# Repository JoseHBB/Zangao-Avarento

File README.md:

# Zangão Avarento

Wiki pública do projeto de TCC de automação industrial focado no desenvolvimento de um drone de baixo custo controlado por smartphone.

## Sobre

O Zangão Avarento nasceu como um projeto de TCC com o objetivo de demonstrar que era possível montar uma plataforma de voo com controle por celular utilizando componentes acessíveis, fabricação própria da placa e desenvolvimento do firmware e do aplicativo.

Este repositório funciona como a documentação pública do projeto. Aqui estão reunidos o histórico de desenvolvimento, os arquivos de eletrônica e PCB, os códigos do Arduino, os arquivos do aplicativo, imagens do processo e o relatório final.

## Navegação da wiki

- [Visão geral do projeto](Projeto.md)
- [Construção mecânica e estrutura](Construcao_Mecanica.md)
- [Firmware e lógica de controle no Arduino](Arduino_Reference.md)
- [Esquema elétrico e PCB no KiCad](KicadSchemePCB_Reference.md)
- [Aplicativo Android](App_Reference.md)
- [Galeria de imagens](Galeria.md)
- [Arquivos e recursos do repositório](Arquivos_e_Recursos.md)

## Estrutura resumida

- `Arduino/`: códigos e rascunhos do firmware.
- `App/`: arquivo-fonte do app no MIT App Inventor e APK gerado.
- `Kicad Scheme-PCB/`: projeto eletrônico e layout da placa.
- `Images/`: imagens de protótipos, placa, estrutura e esquemas.
- `Videos/`: vídeos de testes das funções e demonstração de voo.
- `Apresentação TCC Drone.pptx`: apresentação final do TCC.
- `Relatório.pdf`: versão do relatório final do trabalho.

## Criadores do projeto

- Guilherme Faria da Silva
- João Vinícius da Silva
- José Henrique Batista Borges

## Contato

Qualquer dúvida sobre o projeto:

- [José Henrique](https://github.com/JoseHBB)
- `josehenribb@gmail.com`

## Licença

Este repositório utiliza a licença MIT para fins de estudo, pesquisa, uso pessoal e uso comercial conforme os termos do arquivo [LICENSE](LICENSE).

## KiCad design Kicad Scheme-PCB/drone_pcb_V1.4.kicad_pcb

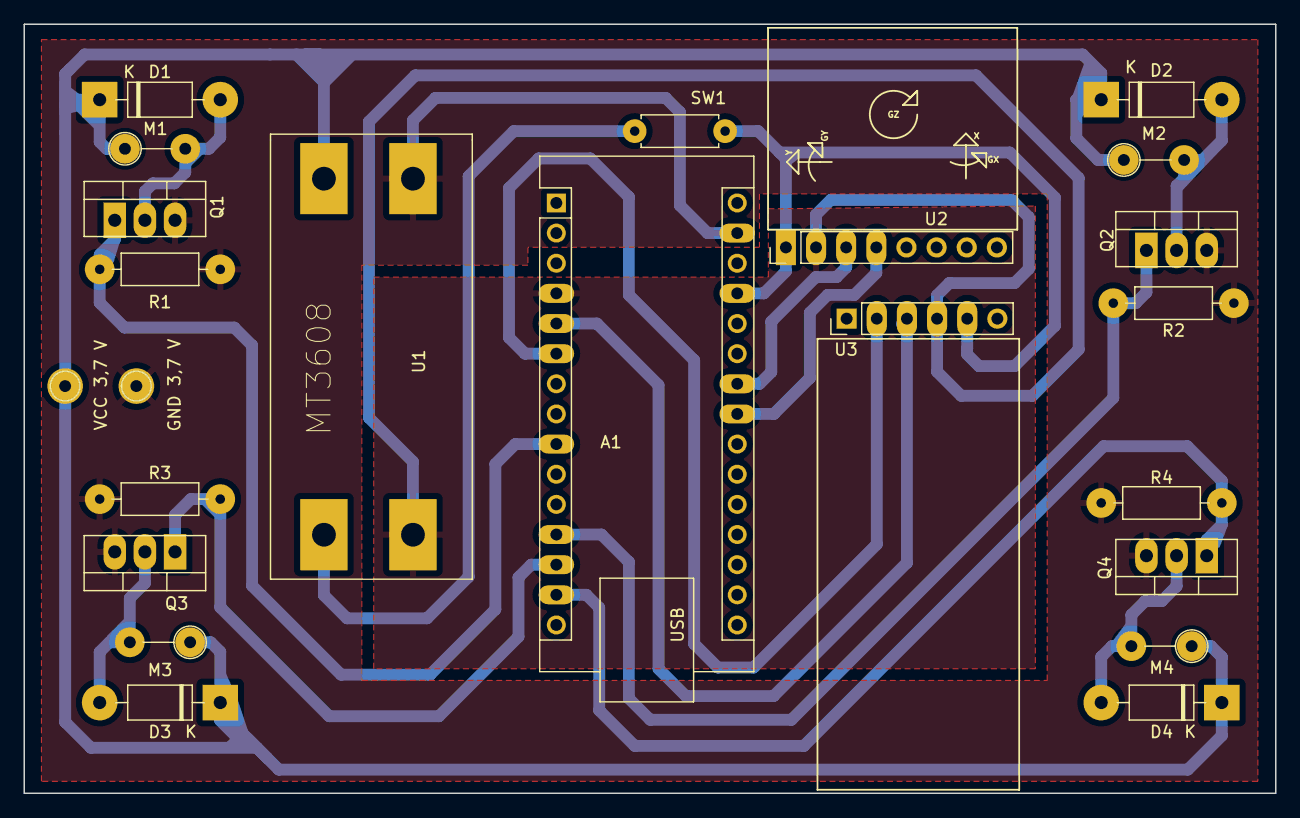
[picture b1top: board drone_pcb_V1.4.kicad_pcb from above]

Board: 2 copper layers, 105.4 x 64.8 mm, 23 parts (0 on the bottom side), 17 nets.

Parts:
A1: Arduino Nano; Arduino_Nano
D1, D2, D3, D4: 1N4007; D_DO-41_SOD81_P10.16mm_Horizontal
GND 3,7 V: Pin_D1.0mm_L10.0mm
M1, M2, M3, M4: Motor; R_Axial_DIN0207_L6.3mm_D2.5mm_P5.08mm_Vertical
Q1, Q2, Q3, Q4: IRF640; TO-220-3_Vertical
R1, R2, R3, R4: 1KΩ; R_Axial_DIN0207_L6.3mm_D2.5mm_P10.16mm_Horizontal
SW1: Switch; R_Axial_DIN0207_L6.3mm_D2.5mm_P7.62mm_Horizontal
U1: Step Up; MT3608
U2: Gyroscope; PinHeader_1x08_P2.54mm_Vertical
U3: HC-06; PinHeader_1x06_P2.54mm_Vertical
VCC 3,7 V: Pin_D1.0mm_L10.0mm

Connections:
GND: A1.29 (GND), GND 3,7 V.1, Q1.3 (S), Q2.3 (S), Q3.3 (S), Q4.3 (S), R1.2, R2.2, R3.2, R4.2, U1.2 (V_in-)
GND_5V: A1.4 (GND), U1.4 (V_out-), U2.2 (GND), U3.4 (GND)
M1-: D1.2 (A), M1.2 (-), Q1.2 (D)
M2-: D2.2 (A), M2.2 (-), Q2.2 (D)
M3-: D3.2 (A), M3.2 (-), Q3.2 (D)
M4-: D4.2 (A), M4.2 (-), Q4.2 (D)
PWM_D6: A1.9 (D6), Q1.1 (G), R1.1
PWM_D9: A1.12 (D9), Q2.1 (G), R2.1
PWM_D10: A1.13 (D10), Q3.1 (G), R3.1
PWM_D11: A1.14 (D11), Q4.3 (G), R4.1
RXD: A1.6 (D3), U3.2 (RXD)
SCL: A1.24 (A5), U2.3 (SCL)
SDA: A1.23 (A4), U2.4 (SDA)
TXD: A1.5 (D2), U3.3 (TXD)
VCC: D1.1 (K), D2.1 (K), D3.1 (K), D4.1 (K), M1.1 (+), M2.1 (+), M3.1 (+), M4.1 (+), U1.1 (V_in+), VCC 3,7 V.1
VCC_5V: SW1.1, U1.3 (V_out+)
VCC_5V_SW: A1.27 (+5V), SW1.2, U2.1 (VCC), U3.5 (VCC)

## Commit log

2024-04-28 Arduino Files
2024-04-28 Esquema do Kicad
2024-04-28 Create LICENSE
2024-04-28 Arduino
2024-04-28 Kicad Scheme & PCB
2024-04-28 LICENSE
2024-04-28 LICENSE
    License Added
2024-04-28 ArduinoReference
2024-04-28 KicadScheme_PCB
2024-04-28 KicadSchemePCB Reference
2024-04-28 Arduino Reference
2024-04-28 Kicad Scheme & PCB Reference
2024-04-28 README.md
2024-04-28 Informações detalhadas sobre o projeto
2024-04-28 Informações gerais do projeto
2024-04-28 Projeto.md
2024-04-28 Aplicativo de smartphone
2024-04-28 App Referencia
2024-04-28 Images
2024-04-28 KicadSchemePCB_Reference.md
2026-04-16 Expand project wiki documentation
2026-04-16 Document project presentation
2026-04-21 Atualiza codigo Arduino, adiciona videos e detalha documentacao
2026-04-21 Adiciona videos web e atualiza links da documentacao
2026-04-21 Revert "Adiciona videos web e atualiza links da documentacao"
    This reverts commit 2972aa312a0a8bb3a47b14579f6f74bde9a4885d.
